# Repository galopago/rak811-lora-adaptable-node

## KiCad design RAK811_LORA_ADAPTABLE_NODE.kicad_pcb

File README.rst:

=======================================================================================================================================
RAK811 based LoRa node, with multiple expansion possibilities and designed to fit inside a generic 83x58x33mm waterproof enclosure box.
=======================================================================================================================================

LoRa node powered by AA batteries ready to install inside an easy to find waterproof enclosure.

Read this in other languages: `Español </docs/README.es.rst>`_

.. image:: /docs/pcb3d.png

Key features:
-------------
* Powered by 2xAA (1.5v) batteries or a single (3.0v) battery.
* Waterproof if installed in an "easy to find worldwide" 83x58x33mm waterproof plastic enclosure (multiple choices: clear cover, wall mounting tabs, etc.).
* Class A battery powered or Class C external powered via screw terminal.
* RAK811 = SX1276+STM32L151. So no additional cpu/microcontroller needed for a complete solution.
* Can be programmed using `RAK Unified Interface (RUI) API, <https://doc.rakwireless.com/quick-start/rak5010-wistrio-nb-iot-tracker/rui-online-compiler>`_ for rapid development or STM32 CUBE LoRa stack.
* TH pad for a spring antenna or U.FL connector for external antenna.
* Prototyping/expansion area.

How to use this repository
--------------------------

The PCB was developed in KiCad V5.1, and include some elements from the official repo.

To setup KiCad to use the downloaded library from the repo instead of the stock that came with the installer, `this post <https://forum.kicad.info/t/library-management-in-kicad-version-5/14636>`_ will give you some lights.

Directory structure
-------------------
* The root folder contains KiCad files: project, schematic and PCB.
* library directory (git submodule) contains schematics symbol libraries.
* modules directory (git submodule) contains footprint libraries.
* packages3d directory (git submodule) contains 3D model libraries.
* gerber/single directory contains ready to manufacture files, for a single board.
* gerber/panel_100mmx100mm directory contains ready to manufacture files that fits in a 100mm x 100mm panel (use Vcuts!).

License
-------

.. image:: https://i.creativecommons.org/l/by/4.0/88x31.png
   :target: http://creativecommons.org/licenses/by/4.0/

This is an Open Hardware project and is licensed under a `Creative Commons Attribution 4.0 International License, <http://creativecommons.org/licenses/by/4.0/>`_

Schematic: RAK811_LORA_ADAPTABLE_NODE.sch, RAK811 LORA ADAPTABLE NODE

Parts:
BT1, BT2: Battery_Cell; BatteryHolder_Keystone_2460_1xAA
H2, H3, H4, H5: MountingHole; MountingHole_3mm
J1, J2: Screw_Terminal_01x03; TerminalBlock_4Ucon_1x03_P3.50mm_Horizontal
J3, J4: Conn_01x03_Male; PinHeader_1x03_P2.54mm_Vertical
J5, J8: Conn_01x11_Male; PinHeader_1x11_P2.54mm_Vertical
J6, J9: Conn_01x01_Male; PinHeader_1x01_P2.54mm_Vertical
J7: Conn_Coaxial; U.FL_Hirose_U.FL-R-SMT-1_Vertical
J10, J11, J12: Conn_01x09_Male; PinHeader_1x09_P2.54mm_Vertical
JP1, JP2: SolderJumper_3_Open; SolderJumper-3_P1.3mm_Open_RoundedPad1.0x1.5mm_NumberLabels
U1: RAK811-HF; RAK811

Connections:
unnamed: BT1.1 (+), JP1.1 (A)
unnamed: BT1.2 (-), BT2.1 (+), JP1.3 (B)
unnamed: BT2.2 (-), J1.2, J7.2 (Ext), J8.11, U1.1 (GND), U1.12 (GND), U1.21 (GND), U1.28 (GND), U1.29 (GND), U1.30 (GND), U1.31 (GND), U1.32 (GND), U1.34 (GND)
unnamed: J1.1, J9.1
unnamed: J1.3, J8.10, JP1.2 (C), U1.11 (VCC)
unnamed: J2.1, J3.1
unnamed: J2.2, J3.2
unnamed: J2.3, J3.3
unnamed: J4.1, U1.15 (PB3)
unnamed: J4.2, U1.14 (PA15)
unnamed: J4.3, U1.13 (PA14)
unnamed: J5.1, U1.16 (PB5)
unnamed: J5.2, U1.17 (BOOT0)
unnamed: J5.3, U1.18 (PB8)
unnamed: J5.4, U1.19 (PB9)
unnamed: J5.5, U1.20 (PA2)
unnamed: J5.6, U1.22 (PA1)
unnamed: J5.7, U1.23 (PA0)
unnamed: J5.8, U1.24 (RST)
unnamed: J5.9, U1.25 (PB10)
unnamed: J5.10, U1.26 (PB11)
unnamed: J5.11, U1.27 (PB2/BOOT1)
unnamed: J6.1, JP2.1 (A)
unnamed: J7.1 (In), JP2.3 (B)
unnamed: J8.1, U1.2 (PB12)
unnamed: J8.2, U1.3 (PB14)
unnamed: J8.3, U1.4 (PB15)
unnamed: J8.4, U1.5 (PA8)
unnamed: J8.5, U1.6 (PA9/USART1_TX)
unnamed: J8.6, U1.7 (PA10/USART1_RX)
unnamed: J8.7, U1.8 (PA12/USART1_RTS)
unnamed: J8.8, U1.9 (PB4/USART1_CTS)
unnamed: J8.9, U1.10 (PA13)
unnamed: JP2.2 (C), U1.33 (RF_OUT)

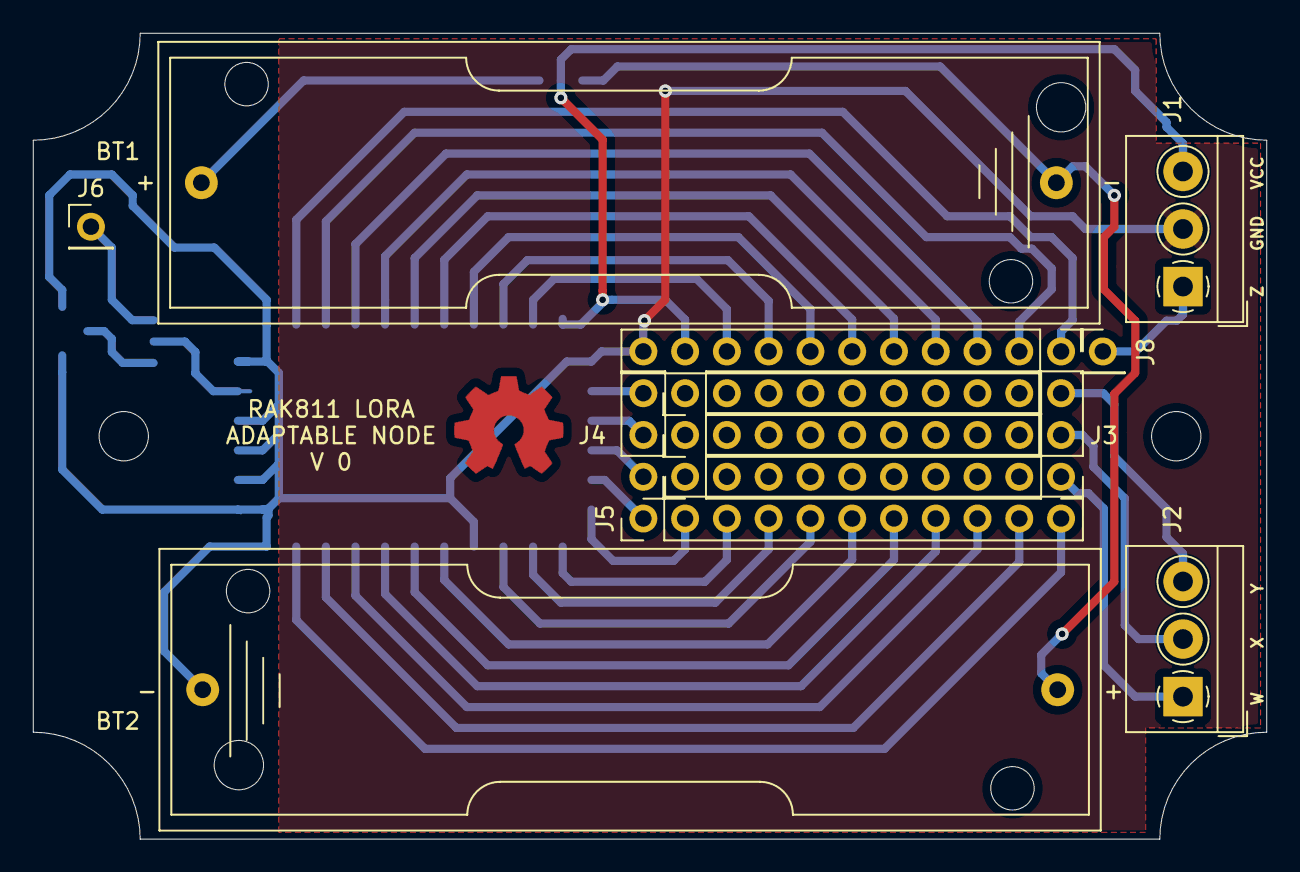
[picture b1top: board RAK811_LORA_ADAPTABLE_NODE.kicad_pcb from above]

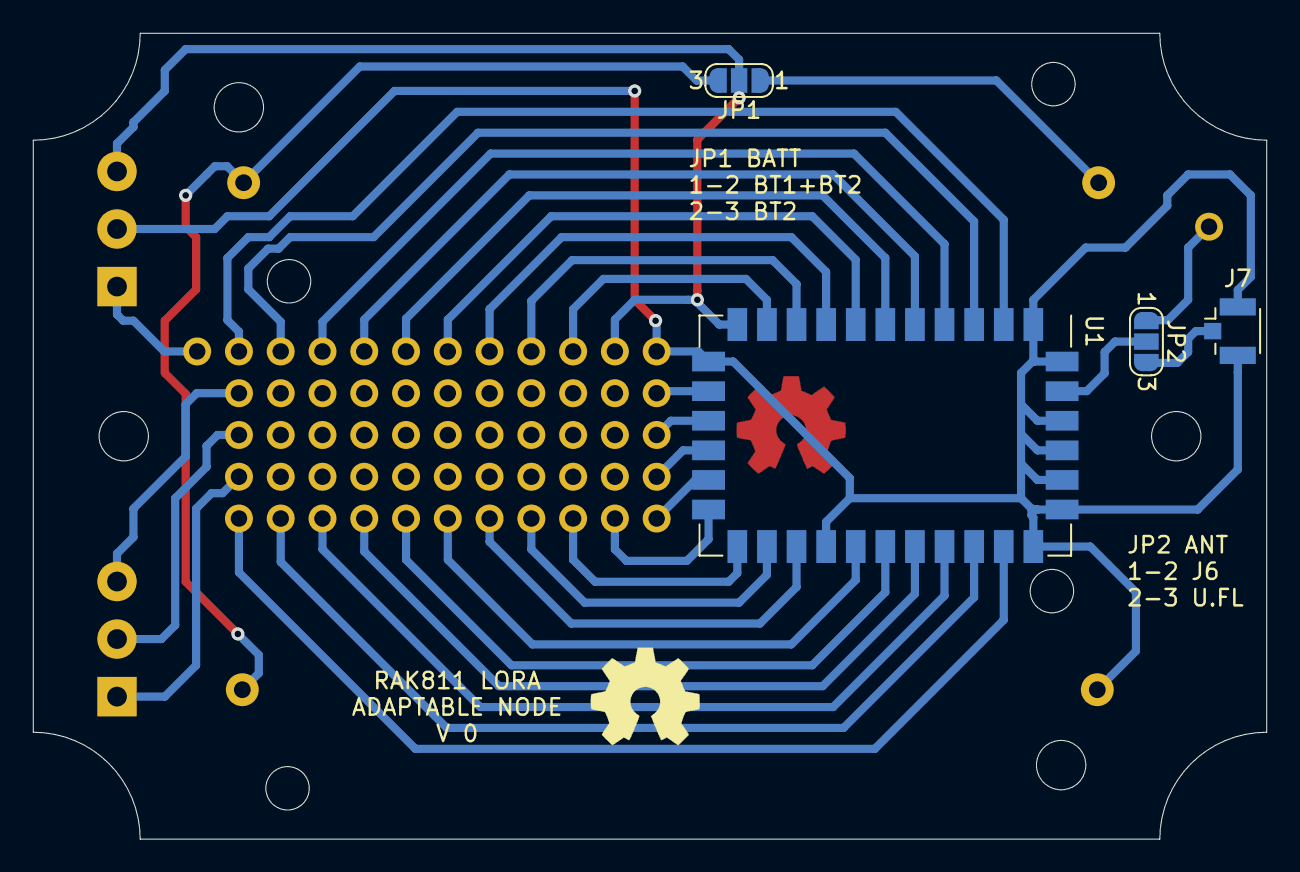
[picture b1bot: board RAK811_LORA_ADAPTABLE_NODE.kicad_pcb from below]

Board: 2 copper layers, 75.0 x 49.0 mm, 21 parts (4 on the bottom side), 34 nets.

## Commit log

2020-06-23 started project from template
2020-06-23 put basic elements: lora mudule, battery holders, screw connectors
2020-06-23 RAK811 updated with improved pin1 silkscreen
2020-06-23 RAK811 updated with improved pin1 fab layer
2020-06-23 RAK811 updated datasheet link to FP description
2020-06-24 add antenna output connectors
2020-06-25 some i/o pins layout
2020-06-25 half i/o pins layout
2020-06-25 all i/o pins layout
2020-06-26 3 of 4 i/o connectors changed from individual to row
2020-06-26 all i/o routed, some battery fine tuning traces todo
2020-06-30 all traces routed
2020-06-30 osw logo
2020-07-01 Z external connector pad aligned to expansion area connectors
2020-07-01 fine tuned routing
2020-07-01 100mm x 10mm panel gerbers
2020-07-02 single board gerbers
2020-07-03 add submodule schematic sybols with unmerged PR
2020-07-03 changed submodule branch to de modified
2020-07-03 deleted failed submodules
2020-07-03 added symbol submodule with unmgerged pr RAK811
2020-07-03 added footprints submodule with unmgerged pr RAK811
2020-07-04 added packages 3D modules to repo
2020-07-09 added license file
2020-07-09 added README in rst format
2020-07-09 deleted README in md format
2020-07-10 license added to the bottom
2020-07-11 add 3d pcb render pic to readme
2020-07-13 more info about the project repo
2020-07-15 README Spanish version initial version
2020-07-15 started translation of README to Spanish
2020-07-15 help spanish titles translated
2020-07-15 key features Spanish translated
2020-07-15 image fix
2020-07-15 Spanish translation finished
2020-08-18 shifted battery connector
2020-08-18 removed unnecessary svg files
2020-08-18 deleted incorrect svg pinouts
2020-08-18 added corrected svg pinouts
2020-09-21 removed packages3d module
2020-09-21 removed modules module
2020-09-21 removed library module
2020-09-21 removed text about submodules in the readme
2020-09-21 removed text in spanish about submodules
